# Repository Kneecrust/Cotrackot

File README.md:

# Cotrackot
A simple, 40 key, wireless, unibody with T460s Trackpoint compatibility named 'Cotrackot'.
Fell in love with Aki's 'Cocot46+' and it inspired me to design this keyboard.

Some details:
1. Choc v1 - Hotswap - MX spaced - index & inner-index columns set to ortholinear for ideal Trackpoint placement.
2. On/Off switch 'jumper on header style' - Placing the jumper over the left and middle pins connects the battery, placing it over the middle and right pins disconnects the battery.
3. 15° angle between the two sides.
4. Pins exposed for Trackpoint: VCC, GND, CLK (P0), DATA (P1), RST (P9).
5. Custom 3DP LDSA keycaps adjusted for MX spacing.
6. Custom 3DP Trackpoint extension pin optimized for FDM printing.

______
Important note on Ergogen yaml:
GPIO are not correctly assigned. 😅
I dealt with that in Kicad directly rather than doing that in Ergogen.

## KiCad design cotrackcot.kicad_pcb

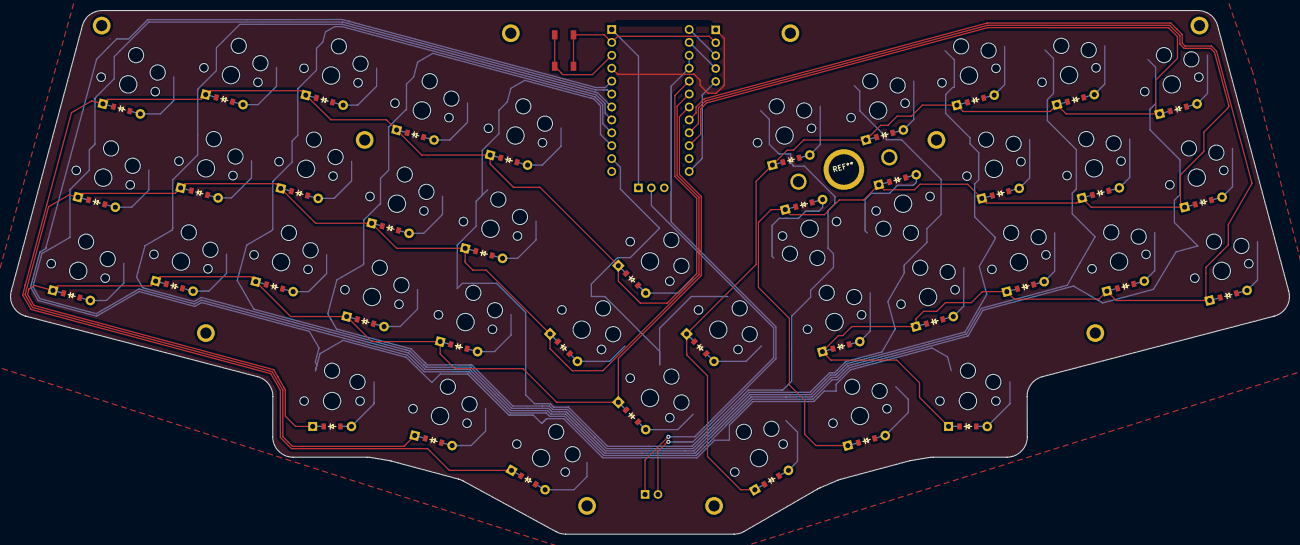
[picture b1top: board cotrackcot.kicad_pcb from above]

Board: 2 copper layers, 251.6 x 103.0 mm, 83 parts (0 on the bottom side), 59 nets.

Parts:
B1: SW_TACT_ALPS_SKQGABE010
D1, D2, D3, D4, D5, D6, D7, D8, D9, D10, D11, D12, D13, D14, D15, D16, D17, D18, D19, D20, D21, D22, D23, D24, D25, D26, D27, D28, D29, D30, D31, D32, D33, D34, D35, D36, D37, D38, D39, D40: ComboDiode
MCU1: ProMicro
S1, S2, S3, S4, S5, S6, S7, S8, S9, S10, S11, S12, S13, S14, S15, S16, S17, S18, S20, S21, S22, S23, S24, S25, S26, S27, S28, S29, S30, S31, S32, S33, S34, S35, S36, S37, S38, S39, S40: PG1350 - Choc Hotswap Basic
S19: PG1350
T460S: T460S; PinHeader_1x05_P2.54mm_Vertical

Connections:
Col_1: MCU1.11, S1.1, S2.1, S3.1, S4.1
Col_2: MCU1.10, S17.1, S18.1, S19.1, S32.1, S33.1, S34.1
Col_3: MCU1.9, S14.1, S15.1, S16.1, S29.1, S30.1, S31.1
Col_4: MCU1.8, S11.1, S12.1, S13.1, S26.1, S27.1, S28.1
Col_5: MCU1.7, S8.1, S9.1, S10.1, S23.1, S24.1, S25.1
Col_6: MCU1.6, S5.1, S6.1, S7.1, S20.1, S21.1, S22.1
Col_7: MCU1.5, S35.1, S36.1, S37.1, S38.1, S39.1, S40.1
GND: B1.1, MCU1.2, MCU1.15, MCU1.16, T460S.2
P0: MCU1.14, T460S.4
P1: MCU1.13, T460S.3
P9: MCU1.24, T460S.5
RST: B1.2, MCU1.3
Row_1: D4.1, D7.1, D10.1, D13.1, D16.1, D19.1, D37.1, MCU1.17
Row_2: D2.1, D6.1, D9.1, D12.1, D15.1, D18.1, D36.1, MCU1.18
Row_3: D1.1, D5.1, D8.1, D11.1, D14.1, D17.1, D35.1, MCU1.19
Row_4: D3.1, D22.1, D25.1, D28.1, D31.1, D34.1, D40.1, MCU1.22
Row_5: D21.1, D24.1, D27.1, D30.1, D33.1, D39.1, MCU1.21
Row_6: D20.1, D23.1, D26.1, D29.1, D32.1, D38.1, MCU1.20
VCC: MCU1.4, T460S.1
home_home: D36.2, S36.2
index_bottom: D14.2, S14.2
index_home: D15.2, S15.2
index_top: D16.2, S16.2
inner_bottom: D17.2, S17.2
inner_home: D18.2, S18.2
inner_home_thumb_left: D35.2, S35.2
inner_top: D19.2, S19.2
left_bottom: D2.2, S2.2
left_home: D1.2, S1.2
middle_bottom: D11.2, S11.2
middle_home: D12.2, S12.2
middle_top: D13.2, S13.2
mirror_home_home: D39.2, S39.2
mirror_index_bottom: D29.2, S29.2
mirror_index_home: D30.2, S30.2
mirror_index_top: D31.2, S31.2
mirror_inner_bottom: D32.2, S32.2
mirror_inner_home: D33.2, S33.2
mirror_inner_home_thumb: D38.2, S38.2
mirror_inner_top: D34.2, S34.2
mirror_middle_bottom: D26.2, S26.2
mirror_middle_home: D27.2, S27.2
mirror_middle_top: D28.2, S28.2
mirror_outer_home: D40.2, S40.2
mirror_pinky_bottom: D20.2, S20.2
mirror_pinky_home: D21.2, S21.2
mirror_pinky_top: D22.2, S22.2
mirror_ring_bottom: D23.2, S23.2
mirror_ring_home: D24.2, S24.2
mirror_ring_top: D25.2, S25.2
outer_home: D37.2, S37.2
pinky_bottom: D5.2, S5.2
pinky_home: D6.2, S6.2
pinky_top: D7.2, S7.2
right_bottom: D4.2, S4.2
right_home: D3.2, S3.2
ring_bottom: D8.2, S8.2
ring_home: D9.2, S9.2
ring_top: D10.2, S10.2

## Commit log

2024-11-21 First Upload
2024-11-21 Update README.md
    Disclaimer on Ergogen Yaml.
